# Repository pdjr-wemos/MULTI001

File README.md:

# MULTI001
 
__MULTI001__ is an MQTT wireless sensor module based on the
[Wemos D1]()...

The module can be connected to the following sensor devices and will
report readings from the connected devices over MQTT.

**AM2320** is connects to the I2C terminals and supplies temperature
and humidity readings.

**DS18B20** connects to the DS terminals and supplies temperature
readings.

**SmartDim** is a movement/occupancy sensor which can be connected
to the SDIM terminals and supplies lux and occupancy readings.

Additionally, up to four active-low SPST switches can be connected
to the CO, SW0, SW1, SW2 and SW3 terminals to provide switch state
readings.

BROWN  - +12VDC power-in\
YELLOW - GND\
ORANGE - PIR (normally 0VDC, 12VDC pulse when movement detected)\
YELLOW - LUX (0 - 12VDC representing LUX level)\
 
__MULTI001__ obtains temperature data from a DS18B20 digital thermometer.

## Installation

Connect the sensor module's power input terminals to a DC supply
voltage between 9VDC and 24VDC.

The module has an intermittent maximum power consumption of 500mW.

## Configuration

When powered for the first time __MULTI001__ launches a wireless access
point with an SSID of the form "MULTISENSOR-*mac-address*".
The access point implements a captive portal web-interface that allows
the user of a WiFi client to enter the following configuration parameters
that will subsequently be used by the sensor in normal operation:

* host network SSID (this can be selected from a scan list)
* host network password
* MQTT server hostname or IP address
* MQTT username, and
* MQTT password that will be used to authenticate publish requests
* MQTT sensor name (defaults to the device MAC address)

## Operation

After configuration, a power cycle on __MULT001__ will cause it to
reboot as a WiFi client on the host network specified during
configuration.
If the module cannot connect to the specified WiFi hotspot within two
minutes, then it will revert to configuration mode.

Once a connection to the host WiFi network is made the module will
immediately begin reporting sensor readings to the MQTT server using the
topic "multisensor/*sensor-name*/status".

The MQTT message payload is a JSON string of the form:

{\
  "temperature": *temperature*, // in degrees celsius\
  "motion": *yesno*, // 0 says no motion detected, 1 says motion detected\
  "lux": *percent* // 0..100 of the sensor range\
}\

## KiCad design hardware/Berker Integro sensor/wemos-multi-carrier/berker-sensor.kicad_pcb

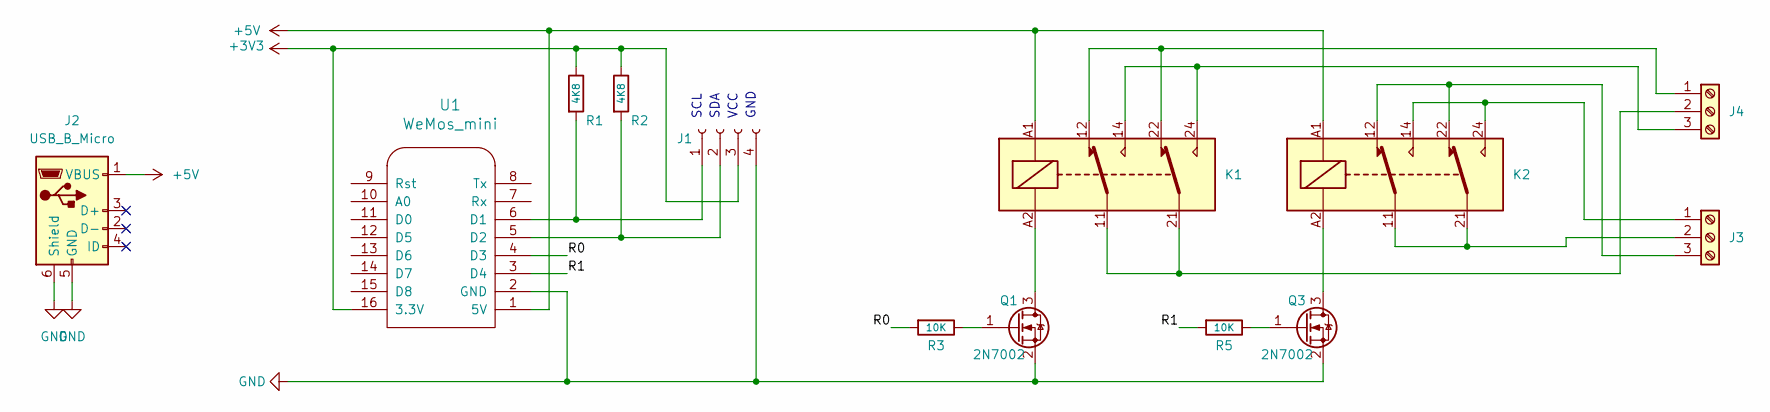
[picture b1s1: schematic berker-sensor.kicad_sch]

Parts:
J1: Conn_01x04_Socket; JST_GH_SM04B-GHS-TB_1x04-1MP_P1.25mm_Horizontal
J2: USB_B_Micro; USB_Micro-B_Wuerth_614105150721_Vertical
J3, J4: Screw_Terminal_01x03; RS_1731204_2.54x3_SCREW_TERMINAL
K1, K2: Relay_DPDT; RS_SUBMINIATURE_SIGNAL_RELAY
Q1, Q3: 2N7002; SOT-23
R1, R2: 4K8; R_0805_2012Metric
R3, R5: 10K; R_0805_2012Metric
U1: WeMos_mini; WEMOS_D1

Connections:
+3V3: J1.3, R1.1, R2.1, U1.16 (3.3V)
+5V: J2.1 (VBUS), K1.A1, K2.A1, U1.1 (5V)
/R0: R3.2, U1.4 (D3)
/R1: R5.2, U1.3 (D4)
GND: J1.4, J2.5 (GND), J2.6 (Shield), Q1.2 (S), Q3.2 (S), U1.2 (GND)
unnamed: J1.1, R1.2, U1.6 (D1)
unnamed: J1.2, R2.2, U1.5 (D2)
unnamed: J3.1, K2.14, K2.24
unnamed: J3.2, K2.11, K2.21
unnamed: J3.3, K2.12, K2.22
unnamed: J4.1, K1.12, K1.22
unnamed: J4.2, K1.11, K1.21
unnamed: J4.3, K1.14, K1.24
unnamed: K1.A2, Q1.3 (D)
unnamed: Q1.1 (G), R3.1
unnamed: K2.A2, Q3.3 (D)
unnamed: Q3.1 (G), R5.1

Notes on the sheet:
SCL
GND
VCC
SDA

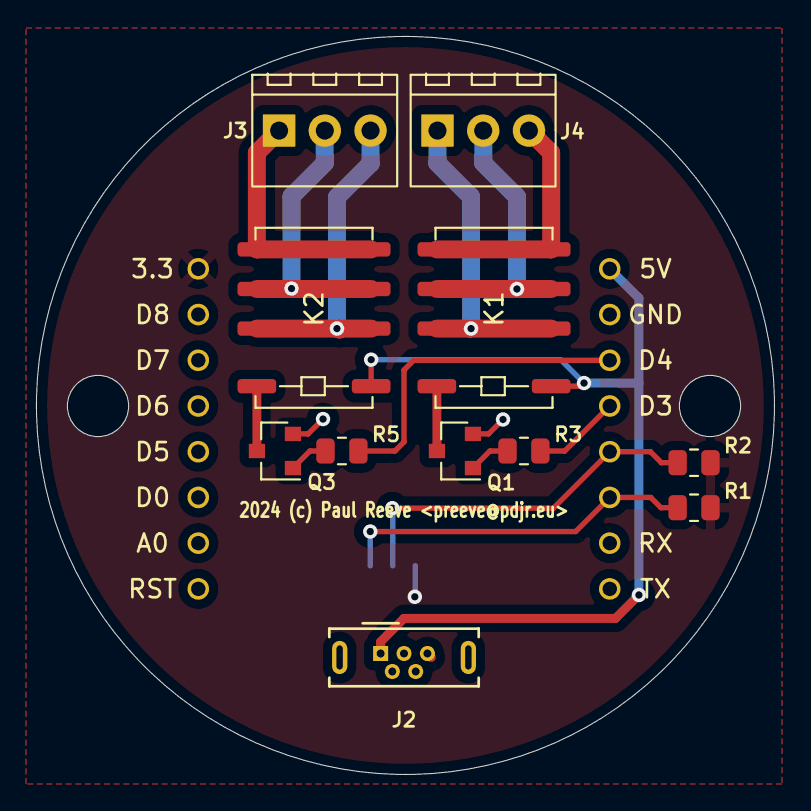
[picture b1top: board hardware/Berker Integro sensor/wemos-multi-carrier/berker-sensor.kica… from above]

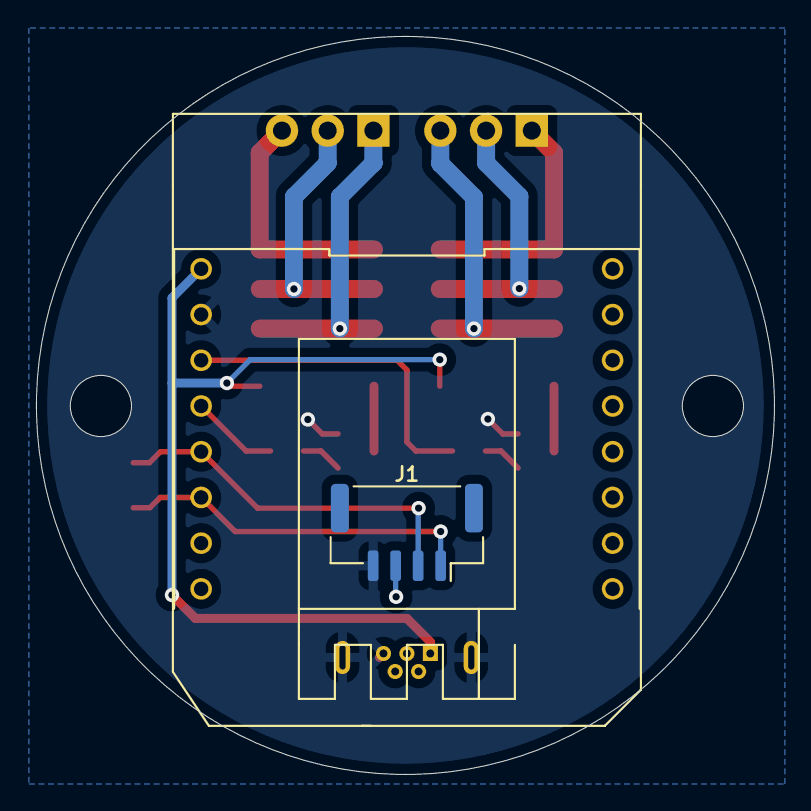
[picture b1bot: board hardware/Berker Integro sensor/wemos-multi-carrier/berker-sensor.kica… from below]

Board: 2 copper layers, 41.0 x 41.0 mm, 13 parts (2 on the bottom side), 17 nets.

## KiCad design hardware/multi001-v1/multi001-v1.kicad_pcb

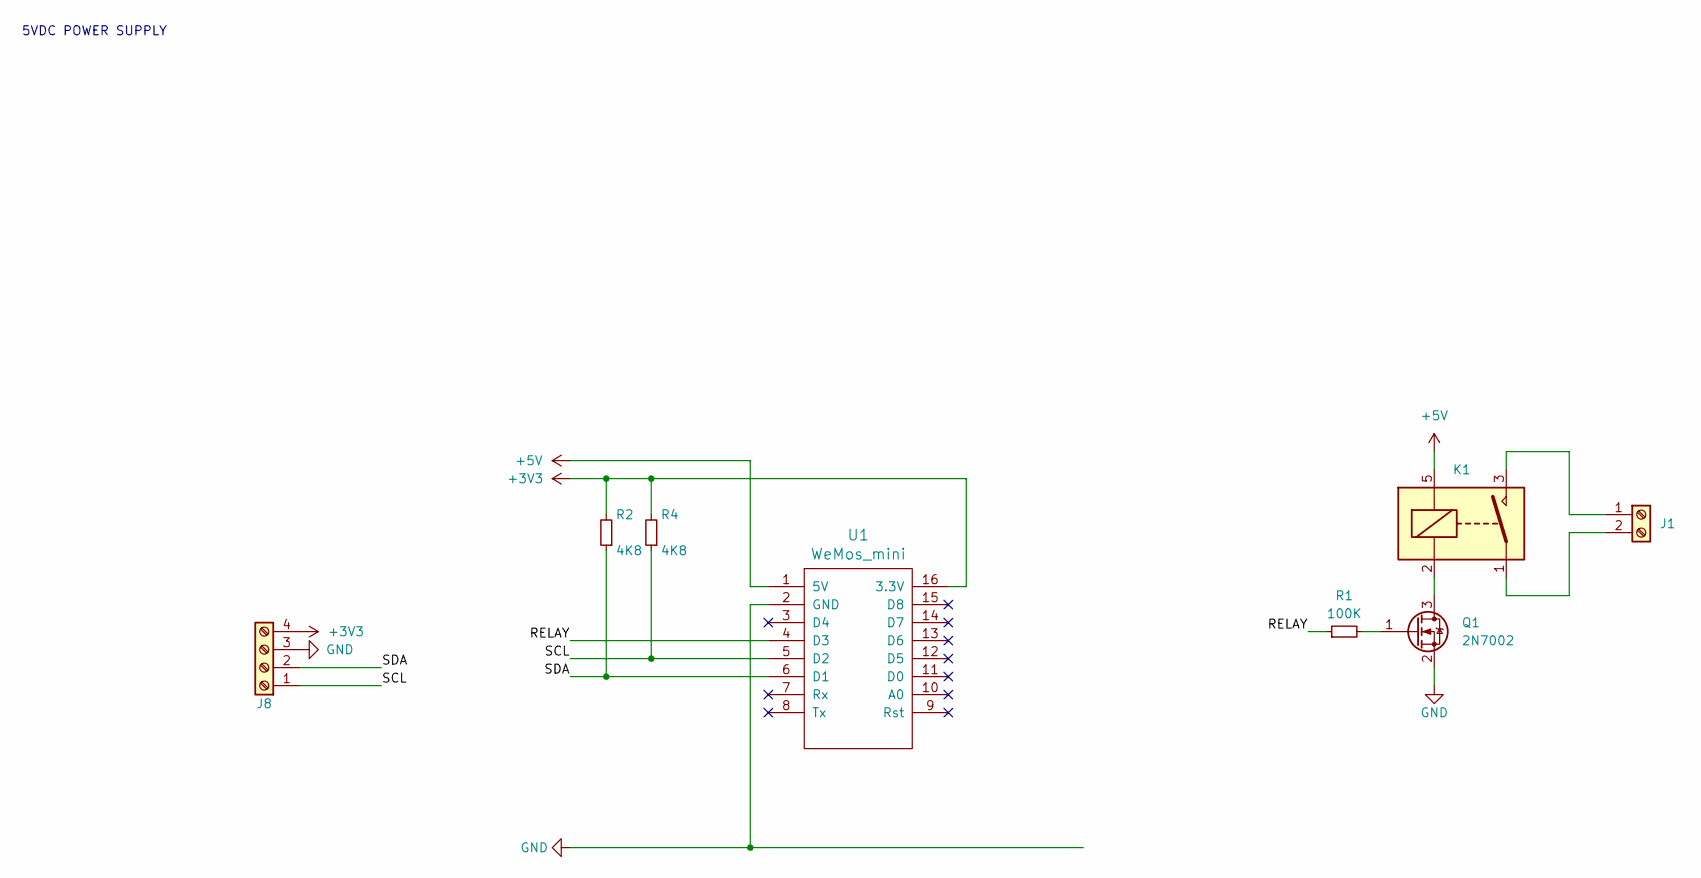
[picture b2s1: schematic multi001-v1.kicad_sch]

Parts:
J1: Screw_Terminal_01x02; PinHeader_1x02_P2.00mm_Vertical_SMD_Pin1Right
J8: Screw_Terminal_01x04; PinHeader_1x04_P2.54mm_Vertical
K1: SANYOU_SRD_Form_A; Relay_SPST_SANYOU_SRD_Series_Form_A
Q1: 2N7002; SOT-23
R1: 100K; R_0805_2012Metric
R2, R4: 4K8; R_0805_2012Metric
U1: WeMos_mini; D1_mini_board

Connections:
+3V3: J8.4, R2.2, R4.2, U1.16 (3.3V)
+5V: K1.5, U1.1 (5V)
/RELAY: R1.1, U1.4 (D3)
/SCL: J8.1, R4.1, U1.5 (D2)
/SDA: J8.2, R2.1, U1.6 (D1)
GND: J8.3, Q1.2 (S), U1.2 (GND)
unnamed 6: J1.1, K1.3; also elsewhere on the board
unnamed 7: J1.2, K1.1; also elsewhere on the board
unnamed: K1.2, Q1.3 (D)
unnamed: Q1.1 (G), R1.2

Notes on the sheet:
5VDC POWER SUPPLY

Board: 2 copper layers, 9 parts (0 on the bottom side), 10 nets, no tracks yet.

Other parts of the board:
J1#2: Screw_Terminal_01x02; PinHeader_1x02_P2.00mm_Vertical_SMD_Pin1Right

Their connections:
unnamed 6: J1#2.1; also elsewhere on the board
unnamed 7: J1#2.2; also elsewhere on the board

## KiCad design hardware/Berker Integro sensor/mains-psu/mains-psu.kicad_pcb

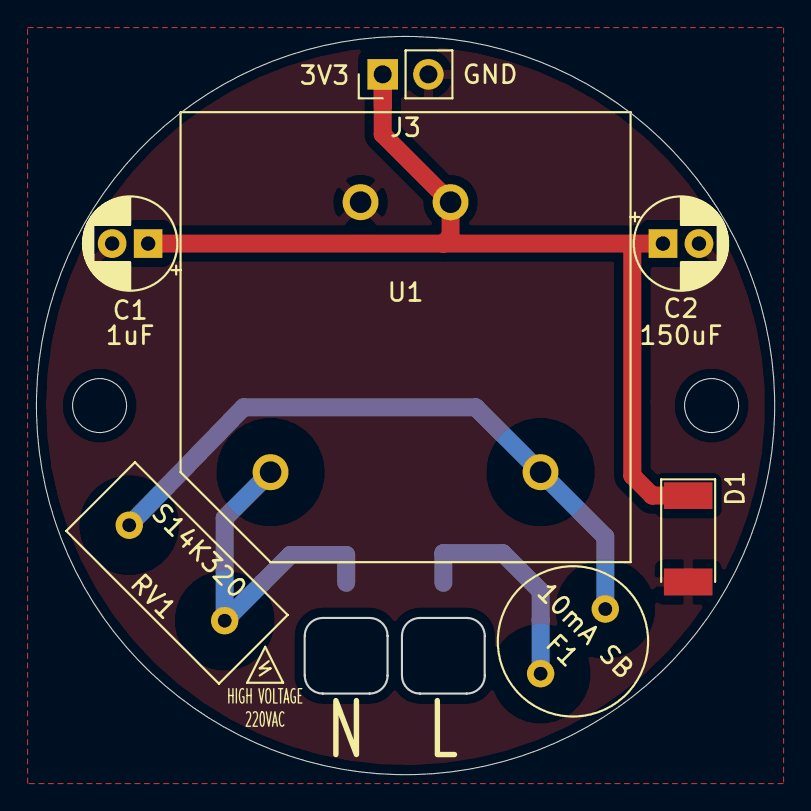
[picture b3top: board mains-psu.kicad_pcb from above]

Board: 2 copper layers, 40.9 x 40.9 mm, 9 parts (0 on the bottom side), 5 nets.

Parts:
C1: 1uF; CP_Radial_D5.0mm_P2.00mm
C2: 150uF; CP_Radial_D5.0mm_P2.00mm
D1: D_Zener; D_MELF
F1: 10mA SB; BEL_MRT_SERIES
J1, J2: Conn_01x01; KYOCERA_POKEHOME_1P
J3: Conn_01x02; PinHeader_1x02_P2.54mm_Vertical
RV1: S14K320
U1: VTX-214-001-105; VTX-214-003-703

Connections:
+3V3: C1.1, C2.1, D1.1, J3.1, U1.3
GND: C1.2, C2.2, D1.2, J3.2, U1.4
LINE: F1.2, J1.1
NEUT: J2.1, RV1.2, U1.1
unnamed: F1.1, RV1.1, U1.2

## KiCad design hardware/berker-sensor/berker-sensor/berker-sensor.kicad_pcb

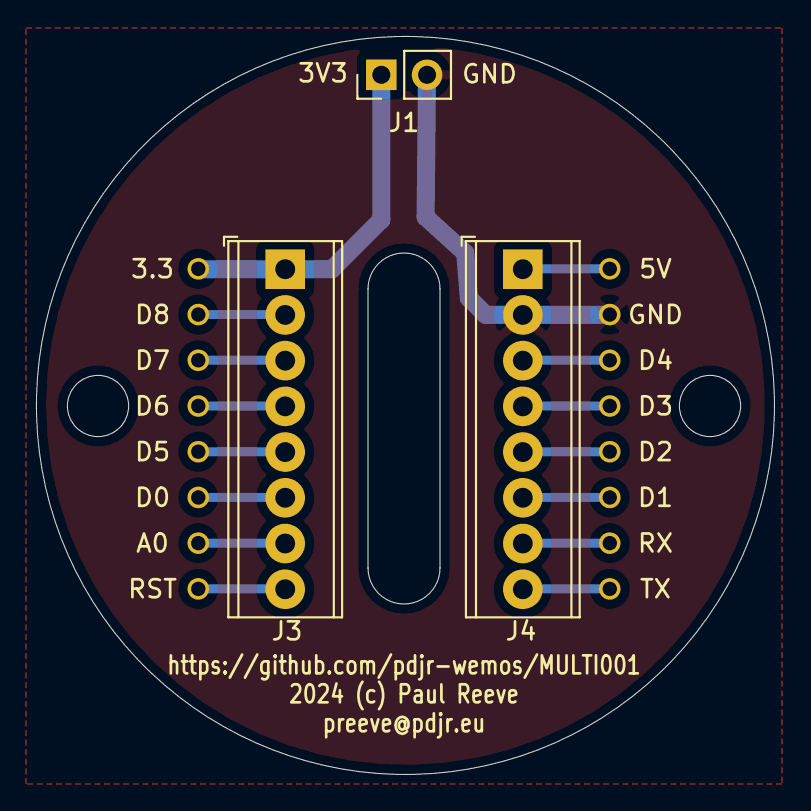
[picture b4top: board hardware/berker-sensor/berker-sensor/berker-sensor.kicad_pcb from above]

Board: 2 copper layers, 41.0 x 41.0 mm, 4 parts (1 on the bottom side), 16 nets.

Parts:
J1: Conn_01x02; PinHeader_1x02_P2.54mm_Vertical
J3, J4: Conn_01x08_Male; TerminalBlock_Phoenix_MPT-0,5-8-2.54_1x08_P2.54mm_Horizontal
U1: WeMos_mini; WEMOS_D1

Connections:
+3V3: J1.1, J3.1, U1.16
GND: J1.2, J4.2, U1.2
unnamed: J3.2, U1.15
unnamed: J3.3, U1.14
unnamed: J3.4, U1.13
unnamed: J3.5, U1.12
unnamed: J3.6, U1.11
unnamed: J3.7, U1.10
unnamed: J3.8, U1.9
unnamed: J4.1, U1.1
unnamed: J4.3, U1.3
unnamed: J4.4, U1.4
unnamed: J4.5, U1.5
unnamed: J4.6, U1.6
unnamed: J4.7, U1.7
unnamed: J4.8, U1.8

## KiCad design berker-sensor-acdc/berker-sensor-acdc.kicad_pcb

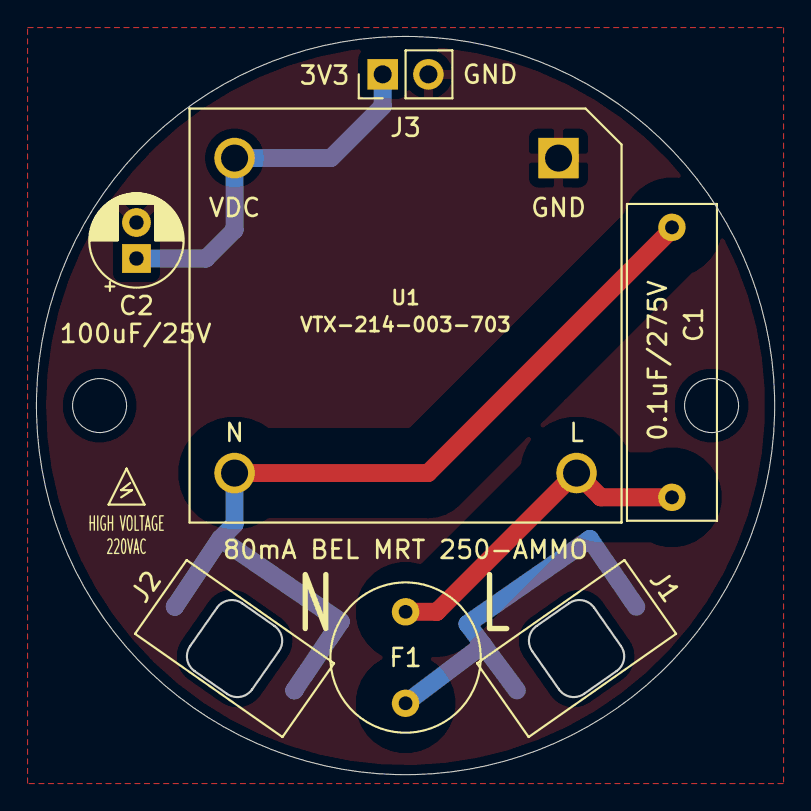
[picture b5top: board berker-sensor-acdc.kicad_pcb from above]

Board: 2 copper layers, 40.9 x 40.9 mm, 7 parts (0 on the bottom side), 5 nets.

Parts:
C1: 0.1uF/275V; PANASONIC_100nF_275VAC
C2: 100uF/25V; CP_Radial_D5.0mm_P2.00mm
F1: 80mA BEL MRT 250-AMMO; BEL_MRT_SERIES
J1, J2: Conn_01x01; KYOCERA_POKEHOME_1P
J3: Conn_01x02; PinHeader_1x02_P2.54mm_Vertical
U1: VTX-214-003-703; VTX214001103

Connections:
+3V3: C2.1, J3.1, U1.2
GND: C2.2, J3.2, U1.1
LINE: F1.2, J1.1
NEUT: C1.2, J2.1, U1.3
unnamed: C1.1, F1.1, U1.4

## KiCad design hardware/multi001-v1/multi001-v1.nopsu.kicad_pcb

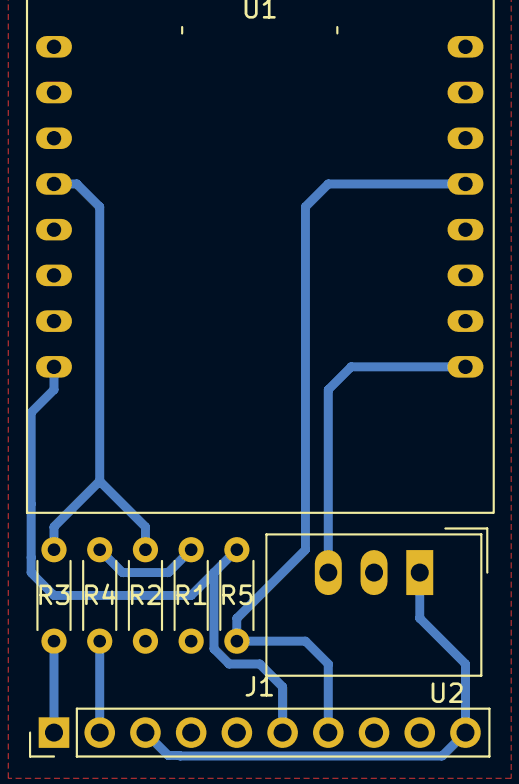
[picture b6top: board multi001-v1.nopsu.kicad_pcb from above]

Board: 2 copper layers, 8 parts (0 on the bottom side), 9 nets.

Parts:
J1: Screw_Terminal_01x10; PinHeader_1x10_P2.54mm_Vertical
R1, R2: 3K2; R_Axial_DIN0204_L3.6mm_D1.6mm_P5.08mm_Horizontal
R3, R4: 9K1; R_Axial_DIN0204_L3.6mm_D1.6mm_P5.08mm_Horizontal
R5: 4K7; R_Axial_DIN0204_L3.6mm_D1.6mm_P5.08mm_Horizontal
U1: D1-MINI-V2; DIP-16_900_ELL
U2: OKI-78SR-5_1.5-W36-C; Converter_DCDC_TRACO_TSR-1_THT

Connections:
/LUX: R1.2, R4.1, U1.2
/PIR: R2.1, R3.1, U1.4
/TEMP: J1.7, R5.2, U1.13
GND: J1.4, J1.8, J1.9, R1.1, R2.2, U1.10, U2.2
unnamed: J1.1, R3.2
unnamed: J1.2, R4.2
unnamed: J1.6, R5.1, U1.8
unnamed: J1.3, J1.10, U2.1
unnamed: U1.9, U2.3

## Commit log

2021-06-28 First upload
2021-06-29 Tweaks...
2021-06-29 Stuff
2021-07-02 Tweaks
2022-01-28 New module type
2022-01-29 Use JSON libraries
2022-01-29 Revision
2022-01-29 Tidy up
2022-01-29 Comments
2022-01-31 First working
2023-05-04 Refactor
2023-05-05 Update README.
2023-05-05 Update sym-lib-table
2023-05-06 Library fix
2024-02-06 Enclosure tweak
2024-08-01 Tweak
